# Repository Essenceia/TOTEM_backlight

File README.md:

<picture align="center">
  <source media="(prefers-color-scheme: dark)" srcset="/docs/images/TOTEM_logo_dark.svg">
  <source media="(prefers-color-scheme: light)" srcset="/docs/images/TOTEM_logo_bright.svg">
  
</picture>

<h1 align="center">T O T E M</h1>

Modified version of the wired TOTEM version 0.3 keyboard, reworked for outsourcing assembly to JLCPCB assembly services and modified to include white backlight.

## Backlight 

Adding simple white backlight to the keyboard. 
Since the default development board used as the controller doesn't have any more available pins 
the backlight could not be controlled by a key combination without the need to switch the board.

I debated removing this limitation but decided I decided to not invest the time in fixing this limitation
in favor of investing my time working on designing custom ASIC's. 

As such, the backlight intensity is controlled via a potentiometer accessible by opening the case. 

Since the switches are not symmetrical and only have an opening for the backlight led on the side opposite to the contact pins, placement 
of the led's implies switch direction. 
The original TOTEM layout gave the flexibility of placing the switch in either of two directions :
 
- pins up: connected to the switch shaft, allowing the switch to be swappable
- pins down: switches soldered in place 

I have chosen the **pins up** layout that allows the switch to still be swappable at the cost of requiring the use of the switch shaft.

:warning: The light intensity controlled circuit was dimensioned to fit these specific leds and potentiometer electrical characteristics, as such,
if you wish to re-use this design, you should **not** blindly switch the led's or the potentiometer model. 

## Manifacturability 

### Front face 

I like soldering 0603 led's as much as the next guys.

In other words: I rather do something else with my very limited time on earth, and my rumba is getting indigestion from all of the suckers that have vanished into the dust. 

Luckily, I can outsource the assembly of these components to wonderful pink and place machines, which on top of 
being more patient than me are orders of magnitude more consistent and precise. Such assembly services are 
offered directly by most big PCB manufacturers and for this board I will be going with JLCPCB. 

In order to outsource this work you will need to provide the BOM ( bill of materials ) and POS ( component position file ) files.

#### Bill of materials

Both files are human readable tables, the bill of materials file contains references to components in the JCBPCB component vendor database
as we will be purchasing the components as part of the assembly process. 

| Comment                  | Designator              | Footprint    | JLCPCB Part #（optional） |
|---------------------------|-------------------------|--------------|---------------------------|
| Diodes 1N4148W           | DL1,DL2,DL3,DL4,DL5,    | SOD-123      | C2099                     |
|                           | DL6,DL7,DL8,DL9,DL10,  |              |                           |
|                           | DL11,DL12,DL13,DL14,   |              |                           |
|                           | DL15,DL16,DL17,DL18,   |              |                           |
|                           | DL19,DR1,DR2,DR3,DR4,  |              |                           |
|                           | DR5,DR6,DR7,DR8,DR9,   |              |                           |
|                           | DR10,DR11,DR12,DR13,   |              |                           |
|                           | DR14,DR15,DR16,DR17,   |              |                           |
|                           | DR18,DR19              |              |                           |
| Reset Button, SKHLLCA010 | RSW1,RSW2               | SKHLLCA010   | C139766                   |
| TRRS jack, PJ-320A       | J1,J2                   | PJ-320A      | C2884926                  |
| LED                      | LEDL1,LEDL2,LEDL3,      | KT-0603W     | C2290                     |
|                           | LEDL4,LEDL5,LEDL6,     |              |                           |
|                           | LEDL7,LEDL8,LEDL9,     |              |                           |
|                           | LEDL10,LEDL11,LEDL12,  |              |                           |
|                           | LEDL13,LEDL14,LEDL15,  |              |                           |
|                           | LEDL16,LEDL17,LEDL18,  |              |                           |
|                           | LEDL19,LEDR1,LEDR2,    |              |                           |
|                           | LEDR3,LEDR4,LEDR5,     |              |                           |
|                           | LEDR6,LEDR7,LEDR8,     |              |                           |
|                           | LEDR9,LEDR10,LEDR11,   |              |                           |
|                           | LEDR12,LEDR13,LEDR14,  |              |                           |
|                           | LEDR15,LEDR16,LEDR17,  |              |                           |
|                           | LEDR18,LEDR19          |              |                           |
| Potenciometer            | RV1,RV2                 | GF063P1-B201 | C128076                   |

#### Positional 

The positional file instructs pick and place machines, where and in which orientation each component should be placed on the board. 
These coordinates assume the part assume the footprints on the board are similar to the footprints used in the JCBPCB part database for this part. 
For example, it assumes both footprints are aligned on the orientation of a component. 

Since there where a few disparities between the original footprints and the JCBPCB part's footprints, a few of the footprint and schematic components 
has to been updated.

There is an overview of the result with the parts we will be outsourcing assemly for outlined in blue. 

These parts are : 

- diodes
- push button
- led's
- potentiometer
- jack connectors

## Back face 

Originally, the switch footprint and the switch shaft where part of the same footprint, make it incompatible with the 
footprint coordinate offset system used to automatically generate the positional file. 
As such, I have separated the switch from the switch shaft footprint allowing the generation of a bottom positional file to also outsource
shaft assembly. 

The begin said, JLCPCB doesn't offer assembly on both sides for the time being.
Thus, given the complexity difference I will only be outsourcing assembly of the top side.   

## Paths for improvement

- Switch out the developement board in favor of having more accessible pins : 
    - re-use my known to be good stm32 circuit -> removes the need to solder on the dev board + port QMK or ZMK to board 
        - downside : design will be harder to re-use for the mechanical keyboard community as flashing the firmware now requires a JTAG
    - use another commonly used dev board as a controller 
        - downside : still requires to solder on the dev board 

- Make backlight control be more easily accessible : 
    - rework case to have the potentiometer knob accessible on the side
    - add a switch upstream of the potentiometer and rework the case to have the backlight switch accessible on the side

## Credits

Original TOTEM repo : [https://github.com/GEIGEIGEIST/TOTEM](https://github.com/GEIGEIGEIST/TOTEM)

Credit to github user `geigeigeist` for the original design

## License

This hardware is under the CERN-OHL-P v2 license, see [LICENSE.md](LICENSE.md)

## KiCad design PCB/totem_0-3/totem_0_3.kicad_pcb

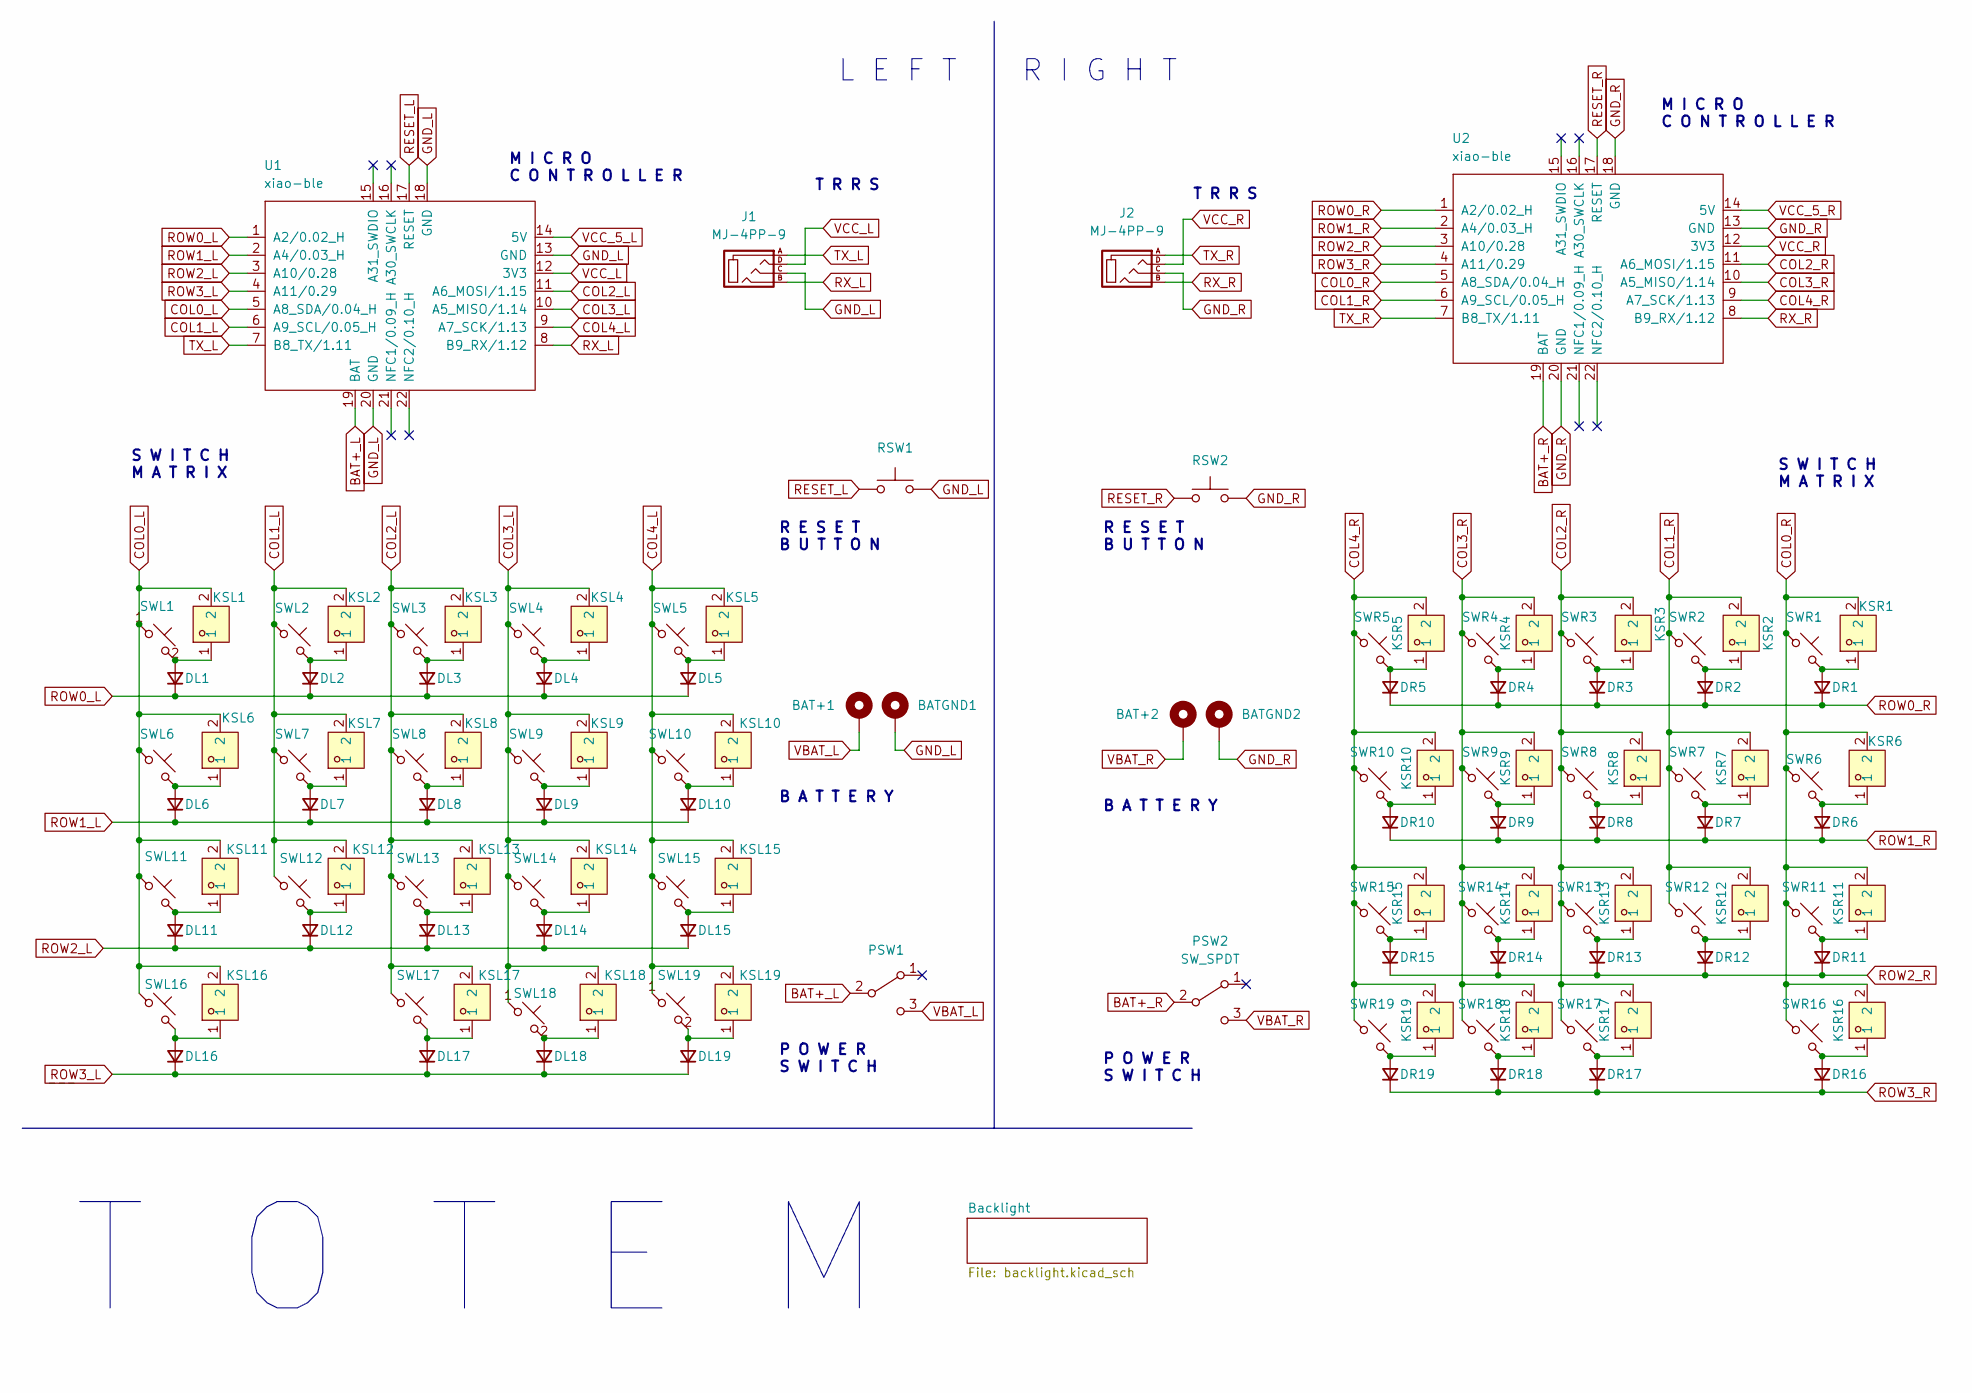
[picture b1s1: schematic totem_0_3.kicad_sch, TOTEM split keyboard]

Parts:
BAT+1, BAT+2: +; BatteryPad
BATGND1, BATGND2: -; BatteryPad
DL1, DL2, DL3, DL4, DL5, DL6, DL7, DL8, DL9, DL10, DL11, DL12, DL13, DL14, DL15, DL16, DL17, DL18, DL19: D_Small; Diode_SOD123
DR1, DR2, DR3, DR4, DR5, DR6, DR7, DR8, DR9, DR10, DR11, DR12, DR13, DR14, DR15, DR16, DR17, DR18, DR19: D_Small; Diode_SOD123
J1, J2: MJ-4PP-9; MJ-4PP-9_1side
KSL1, KSL2, KSL3, KSL4, KSL5, KSL6, KSL7, KSL8, KSL9, KSL10, KSL11, KSL12, KSL13, KSL14, KSL15, KSL16, KSL17, KSL18, KSL19: CPG135001S30; CONN-SMD_HOTPLUGPAKAGE__C9900010116; LCSC Part C5333465
KSR1, KSR2, KSR3, KSR4, KSR5, KSR6, KSR7, KSR8, KSR9, KSR10, KSR11, KSR12, KSR13, KSR14, KSR15, KSR16, KSR17, KSR18, KSR19: CPG135001S30; CONN-SMD_HOTPLUGPAKAGE__C9900010116; LCSC Part C5333465
PSW1, PSW2: SW_SPDT; MSK12C02
RSW1, RSW2: SW_Push; SKHLLCA010
SWL1, SWL2, SWL3, SWL4, SWL5, SWL6, SWL7, SWL8, SWL9, SWL10, SWL11, SWL12, SWL13, SWL14, SWL15, SWL16, SWL17, SWL18, SWL19: SW_Push_45deg; Kailh_socket_PG1350_optional
SWR1, SWR2, SWR3, SWR4, SWR5, SWR6, SWR7, SWR8, SWR9, SWR10, SWR11, SWR12, SWR13, SWR14, SWR15, SWR16, SWR17, SWR18, SWR19: SW_Push_45deg; Kailh_socket_PG1350_optional
U1, U2: xiao-ble; xiao-ble-smd-cutout

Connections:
BAT+_L: PSW1.2 (B), U1.19 (BAT)
BAT+_R: PSW2.2 (B), U2.19 (BAT)
COL0_L: KSL1.2, KSL6.2, KSL11.2, KSL16.2, SWL1.1, SWL6.1, SWL11.1, SWL16.1, U1.5 (A8_SDA/0.04_H)
COL0_R: KSR1.2, KSR6.2, KSR11.2, KSR16.2, SWR1.1, SWR6.1, SWR11.1, SWR16.1, U2.5 (A8_SDA/0.04_H)
COL1_L: KSL2.2, KSL7.2, KSL12.2, SWL2.1, SWL7.1, SWL12.1, U1.6 (A9_SCL/0.05_H)
COL1_R: KSR2.2, KSR7.2, KSR12.2, SWR2.1, SWR7.1, SWR12.1, U2.6 (A9_SCL/0.05_H)
COL2_L: KSL3.2, KSL8.2, KSL13.2, KSL17.2, SWL3.1, SWL8.1, SWL13.1, SWL17.1, U1.11 (A6_MOSI/1.15)
COL2_R: KSR3.2, KSR8.2, KSR13.2, KSR17.2, SWR3.1, SWR8.1, SWR13.1, SWR17.1, U2.11 (A6_MOSI/1.15)
COL3_L: KSL4.2, KSL9.2, KSL14.2, KSL18.2, SWL4.1, SWL9.1, SWL14.1, SWL18.1, U1.10 (A5_MISO/1.14)
COL3_R: KSR4.2, KSR9.2, KSR14.2, KSR18.2, SWR4.1, SWR9.1, SWR14.1, SWR18.1, U2.10 (A5_MISO/1.14)
COL4_L: KSL5.2, KSL10.2, KSL15.2, KSL19.2, SWL5.1, SWL10.1, SWL15.1, SWL19.1, U1.9 (A7_SCK/1.13)
COL4_R: KSR5.2, KSR10.2, KSR15.2, KSR19.2, SWR5.1, SWR10.1, SWR15.1, SWR19.1, U2.9 (A7_SCK/1.13)
GND_L: BATGND1.1, J1.C, RSW1.2, U1.13 (GND), U1.18 (GND), U1.20 (GND); also elsewhere on the board
GND_R: BATGND2.1, J2.C, RSW2.2, U2.13 (GND), U2.18 (GND), U2.20 (GND); also elsewhere on the board
unnamed: DL1.2 (A), KSL1.1, SWL1.2
unnamed: DL2.2 (A), KSL2.1, SWL2.2
unnamed: DL3.2 (A), KSL3.1, SWL3.2
unnamed: DL4.2 (A), KSL4.1, SWL4.2
unnamed: DL5.2 (A), KSL5.1, SWL5.2
unnamed: DL6.2 (A), KSL6.1, SWL6.2
unnamed: DL7.2 (A), KSL7.1, SWL7.2
unnamed: DL8.2 (A), KSL8.1, SWL8.2
unnamed: DL9.2 (A), KSL9.1, SWL9.2
unnamed: DL10.2 (A), KSL10.1, SWL10.2
unnamed: DL11.2 (A), KSL11.1, SWL11.2
unnamed: DL12.2 (A), KSL12.1, SWL12.2
unnamed: DL13.2 (A), KSL13.1, SWL13.2
unnamed: DL14.2 (A), KSL14.1, SWL14.2
unnamed: DL15.2 (A), KSL15.1, SWL15.2
unnamed: DL16.2 (A), KSL16.1, SWL16.2
unnamed: DL17.2 (A), KSL17.1, SWL17.2
unnamed: DL18.2 (A), KSL18.1, SWL18.2
unnamed: DL19.2 (A), KSL19.1, SWL19.2
unnamed: DR1.2 (A), KSR1.1, SWR1.2
unnamed: DR2.2 (A), KSR2.1, SWR2.2
unnamed: DR3.2 (A), KSR3.1, SWR3.2
unnamed: DR4.2 (A), KSR4.1, SWR4.2
unnamed: DR5.2 (A), KSR5.1, SWR5.2
unnamed: DR6.2 (A), KSR6.1, SWR6.2
unnamed: DR7.2 (A), KSR7.1, SWR7.2
unnamed: DR8.2 (A), KSR8.1, SWR8.2
unnamed: DR9.2 (A), KSR9.1, SWR9.2
unnamed: DR10.2 (A), KSR10.1, SWR10.2
unnamed: DR11.2 (A), KSR11.1, SWR11.2
unnamed: DR12.2 (A), KSR12.1, SWR12.2
unnamed: DR13.2 (A), KSR13.1, SWR13.2
unnamed: DR14.2 (A), KSR14.1, SWR14.2
unnamed: DR15.2 (A), KSR15.1, SWR15.2
unnamed: DR16.2 (A), KSR16.1, SWR16.2
unnamed: DR17.2 (A), KSR17.1, SWR17.2
unnamed: DR18.2 (A), KSR18.1, SWR18.2
unnamed: DR19.2 (A), KSR19.1, SWR19.2
RESET_L: RSW1.1, U1.17 (RESET)
RESET_R: RSW2.1, U2.17 (RESET)
ROW0_L: DL1.1 (K), DL2.1 (K), DL3.1 (K), DL4.1 (K), DL5.1 (K), U1.1 (A2/0.02_H)
ROW0_R: DR1.1 (K), DR2.1 (K), DR3.1 (K), DR4.1 (K), DR5.1 (K), U2.1 (A2/0.02_H)
ROW1_L: DL6.1 (K), DL7.1 (K), DL8.1 (K), DL9.1 (K), DL10.1 (K), U1.2 (A4/0.03_H)
ROW1_R: DR6.1 (K), DR7.1 (K), DR8.1 (K), DR9.1 (K), DR10.1 (K), U2.2 (A4/0.03_H)
ROW2_L: DL11.1 (K), DL12.1 (K), DL13.1 (K), DL14.1 (K), DL15.1 (K), U1.3 (A10/0.28)
ROW2_R: DR11.1 (K), DR12.1 (K), DR13.1 (K), DR14.1 (K), DR15.1 (K), U2.3 (A10/0.28)
ROW3_L: DL16.1 (K), DL17.1 (K), DL18.1 (K), DL19.1 (K), U1.4 (A11/0.29)
ROW3_R: DR16.1 (K), DR17.1 (K), DR18.1 (K), DR19.1 (K), U2.4 (A11/0.29)
RX_L: J1.B, U1.8 (B9_RX/1.12)
RX_R: J2.B, U2.8 (B9_RX/1.12)
TX_L: J1.A, U1.7 (B8_TX/1.11)
TX_R: J2.A, U2.7 (B8_TX/1.11)
VBAT_L: BAT+1.1, PSW1.3 (C)
VBAT_R: BAT+2.1, PSW2.3 (C)
VCC_5_L: U1.14 (5V); also elsewhere on the board
VCC_5_R: U2.14 (5V); also elsewhere on the board
VCC_L: J1.D, U1.12 (3V3)
VCC_R: J2.D, U2.12 (3V3)

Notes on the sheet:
M I C R O C O N T R O L L E R
T R R S
R E S E T B U T T O N
S W I T C H M A T R I X
P O W E R S W I T C H
T O T E M
B A T T E R Y
R I G H T
L E F T

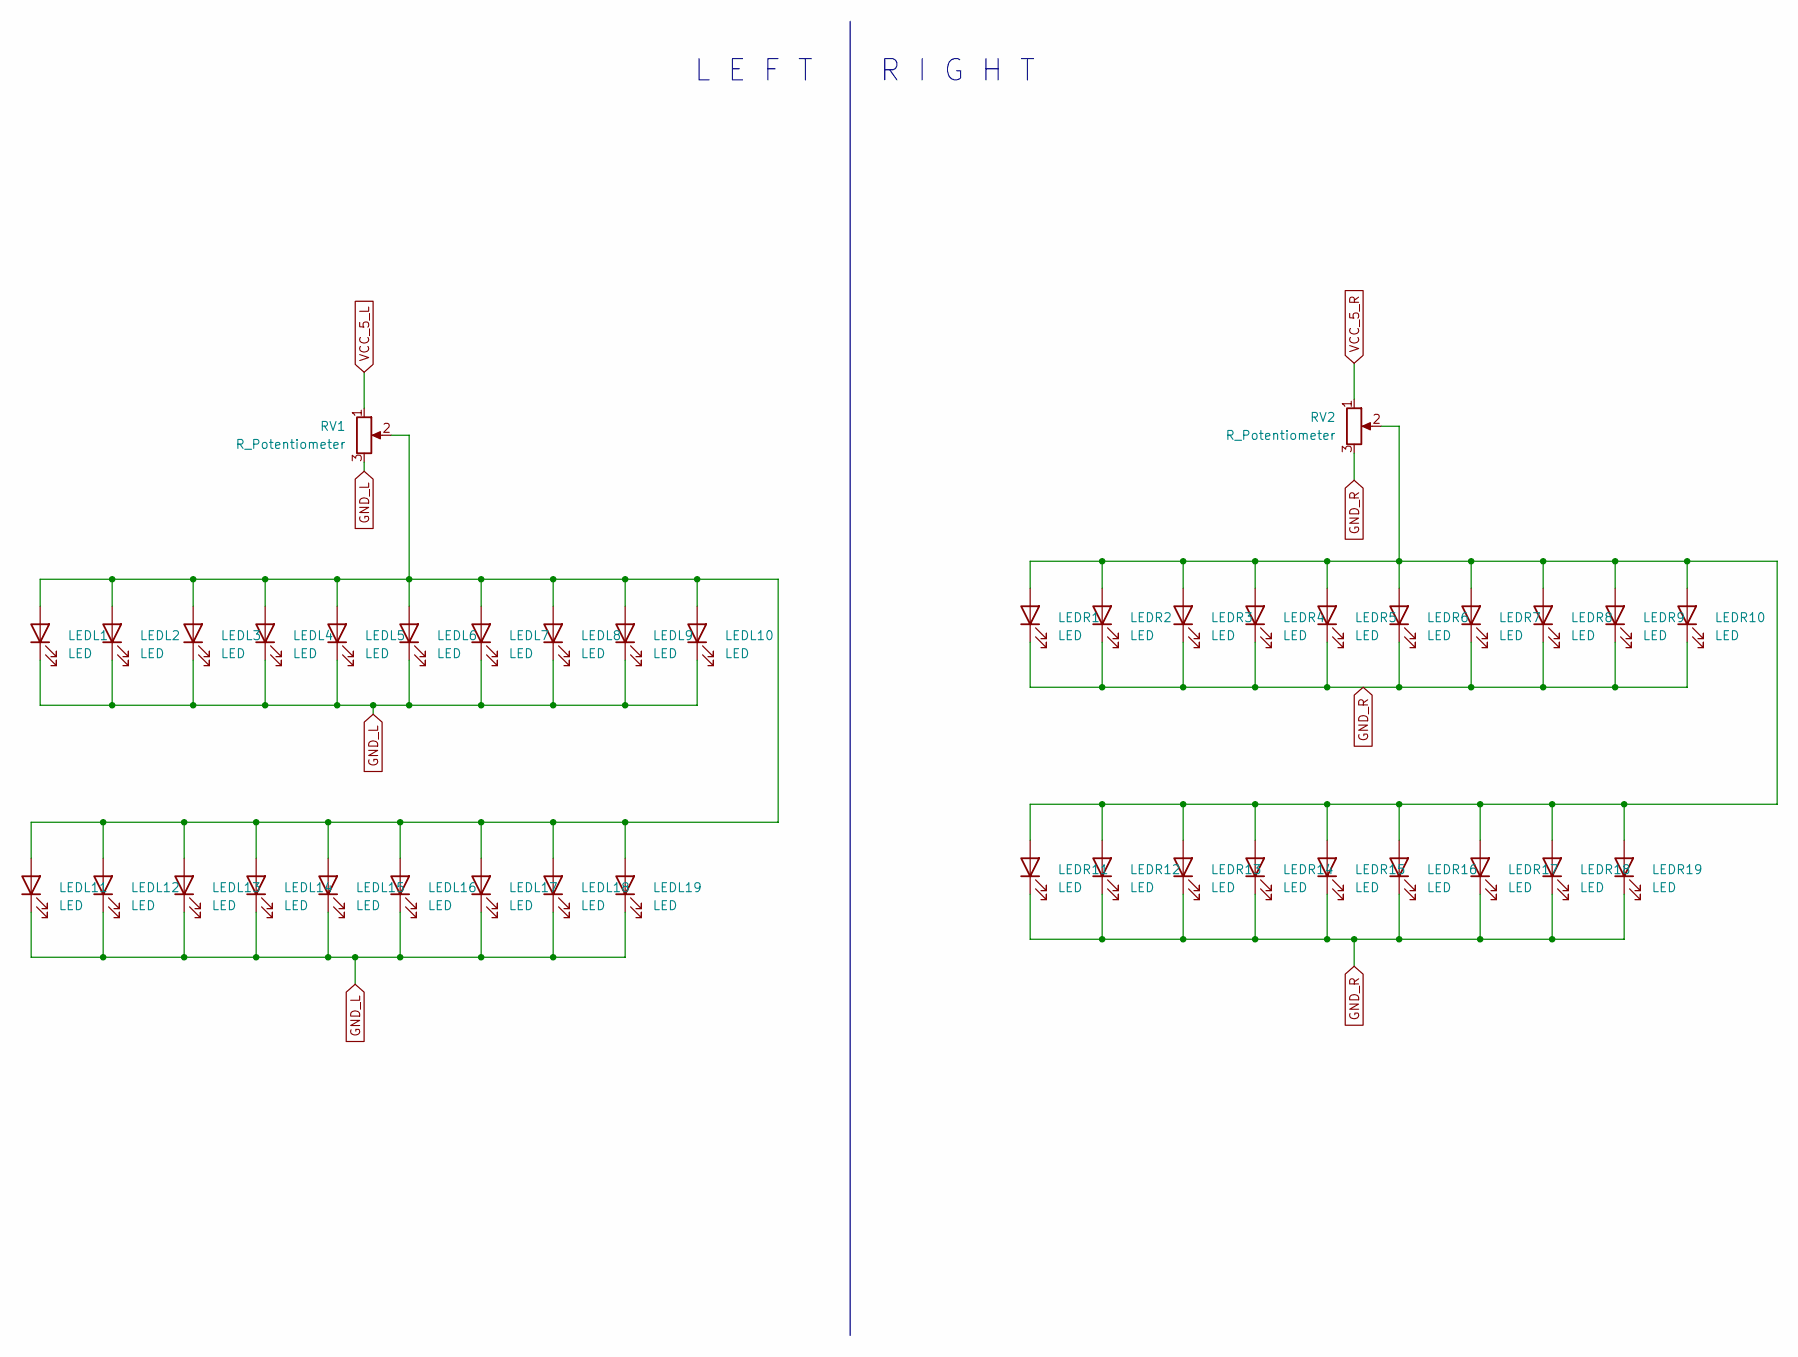
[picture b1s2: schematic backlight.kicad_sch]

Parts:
LEDL1, LEDL2, LEDL3, LEDL4, LEDL5, LEDL6, LEDL7, LEDL8, LEDL9, LEDL10, LEDL11, LEDL12, LEDL13, LEDL14, LEDL15, LEDL16, LEDL17, LEDL18, LEDL19: LED; LED0603-R-RD_WHITE
LEDR1, LEDR2, LEDR3, LEDR4, LEDR5, LEDR6, LEDR7, LEDR8, LEDR9, LEDR10, LEDR11, LEDR12, LEDR13, LEDR14, LEDR15, LEDR16, LEDR17, LEDR18, LEDR19: LED; LED0603-R-RD_WHITE
RV1, RV2: R_Potentiometer; RES-ADJ-SMD_GF063P1

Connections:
GND_L: LEDL1.1 (K), LEDL2.1 (K), LEDL3.1 (K), LEDL4.1 (K), LEDL5.1 (K), LEDL6.1 (K), LEDL7.1 (K), LEDL8.1 (K), LEDL9.1 (K), LEDL10.1 (K), LEDL11.1 (K), LEDL12.1 (K), LEDL13.1 (K), LEDL14.1 (K), LEDL15.1 (K), LEDL16.1 (K), LEDL17.1 (K), LEDL18.1 (K), LEDL19.1 (K), RV1.3; also elsewhere on the board
GND_R: LEDR1.1 (K), LEDR2.1 (K), LEDR3.1 (K), LEDR4.1 (K), LEDR5.1 (K), LEDR6.1 (K), LEDR7.1 (K), LEDR8.1 (K), LEDR9.1 (K), LEDR10.1 (K), LEDR11.1 (K), LEDR12.1 (K), LEDR13.1 (K), LEDR14.1 (K), LEDR15.1 (K), LEDR16.1 (K), LEDR17.1 (K), LEDR18.1 (K), LEDR19.1 (K), RV2.3; also elsewhere on the board
unnamed: LEDL1.2 (A), LEDL2.2 (A), LEDL3.2 (A), LEDL4.2 (A), LEDL5.2 (A), LEDL6.2 (A), LEDL7.2 (A), LEDL8.2 (A), LEDL9.2 (A), LEDL10.2 (A), LEDL11.2 (A), LEDL12.2 (A), LEDL13.2 (A), LEDL14.2 (A), LEDL15.2 (A), LEDL16.2 (A), LEDL17.2 (A), LEDL18.2 (A), LEDL19.2 (A), RV1.2
unnamed: LEDR1.2 (A), LEDR2.2 (A), LEDR3.2 (A), LEDR4.2 (A), LEDR5.2 (A), LEDR6.2 (A), LEDR7.2 (A), LEDR8.2 (A), LEDR9.2 (A), LEDR10.2 (A), LEDR11.2 (A), LEDR12.2 (A), LEDR13.2 (A), LEDR14.2 (A), LEDR15.2 (A), LEDR16.2 (A), LEDR17.2 (A), LEDR18.2 (A), LEDR19.2 (A), RV2.2
VCC_5_L: RV1.1; also elsewhere on the board
VCC_5_R: RV2.1; also elsewhere on the board

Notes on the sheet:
R I G H T
L E F T

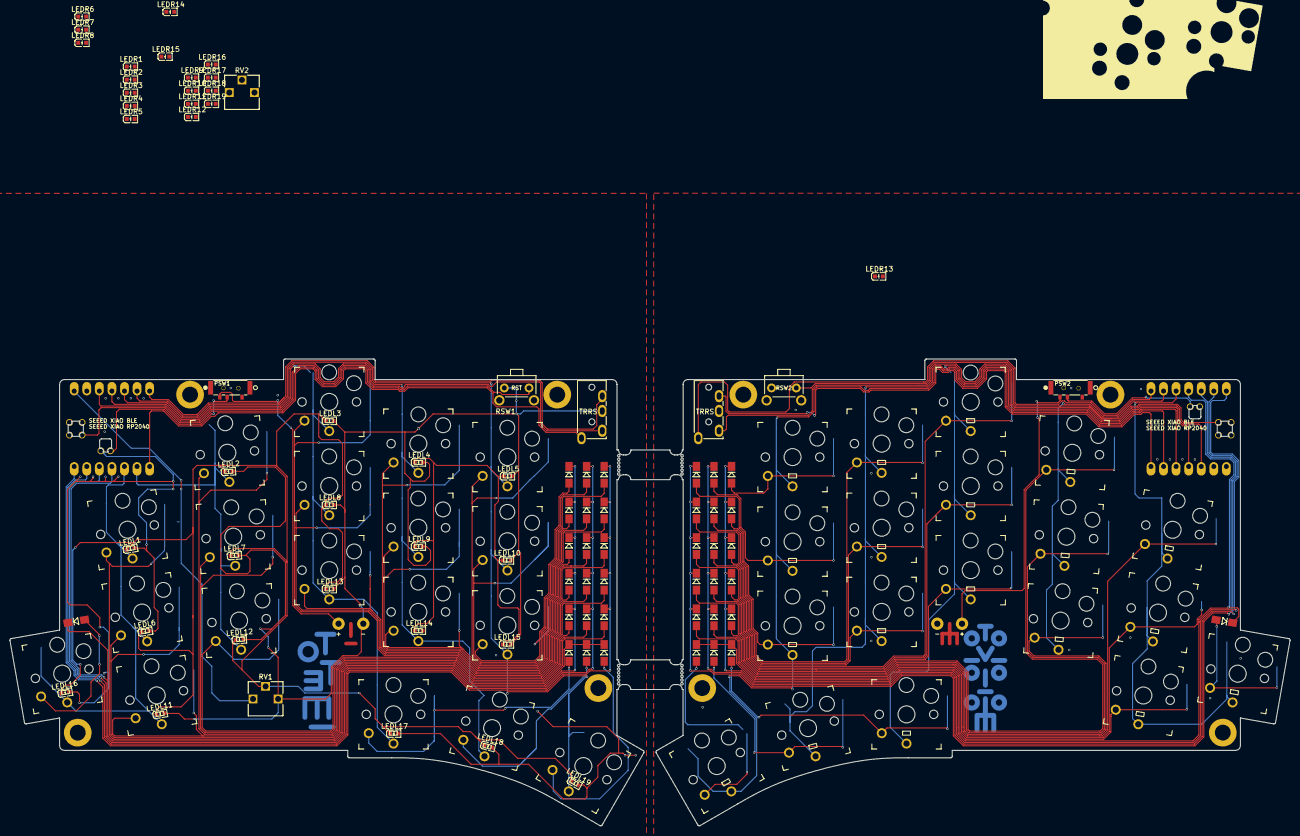
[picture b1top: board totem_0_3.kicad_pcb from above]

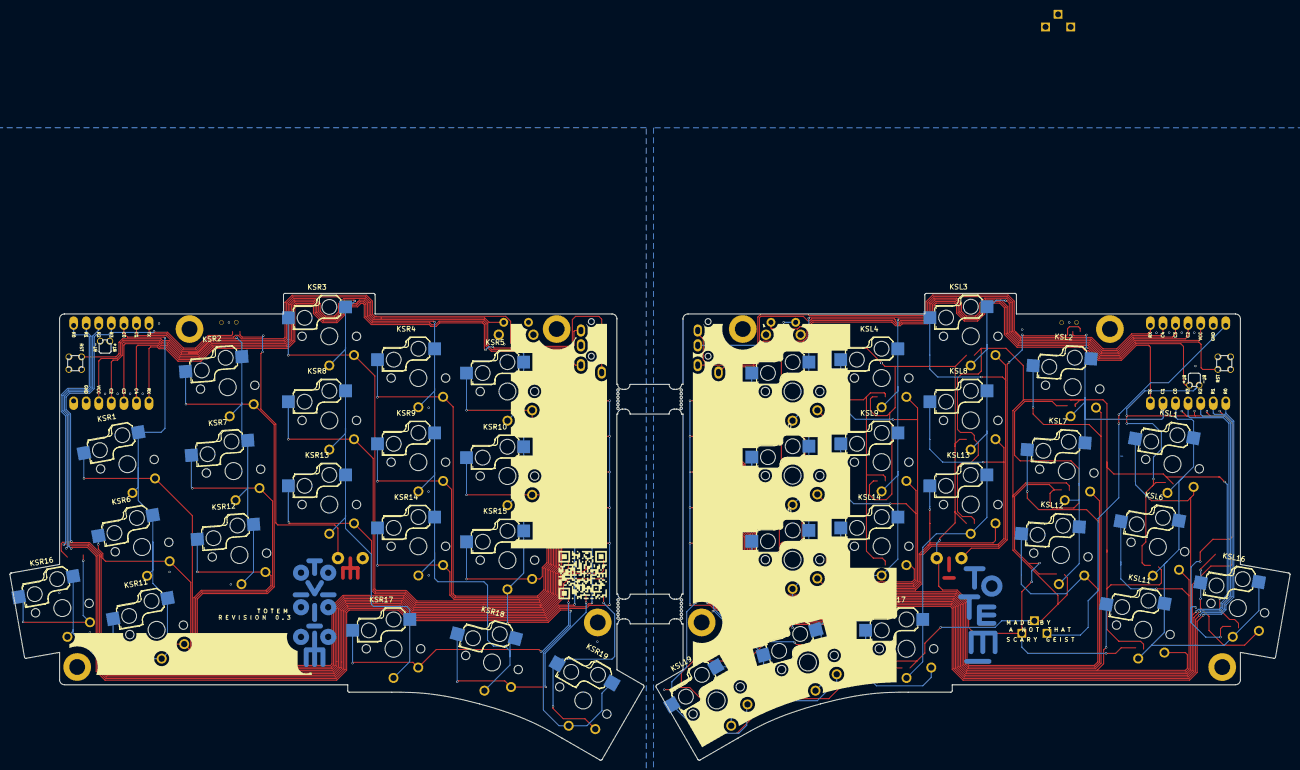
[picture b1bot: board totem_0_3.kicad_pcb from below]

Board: 2 copper layers, 258.7 x 94.4 mm, 166 parts (38 on the bottom side), 74 nets.

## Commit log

2025-08-25 optimising for manifacturability at jlc pcb, seperating connectors from switch footprint
2025-08-26 finished adding switch sockets in the original positions
2025-08-26 adding leds to left, wip
2025-08-27 Adding backlight shematics, wiring left hand, wip
2025-08-28 Finishing wiring, generating placement files for pick and place, modified footprints due to wrong footprint corrdingates at jlcpcb
2025-08-28 add new footprints
2025-08-28 updated backlight shematics with new leds, default led uses reversed pin number assigns, aka : leds get mounted backwards by pick and place, what a tragedy
2025-08-28 updating kicad footprint and shematics
2025-08-28 Updating readme to talk about changes, wip
2025-08-28 Update readme, update gerber renders
2025-08-29 update readme, wip
2025-08-29 Update readme, update license, keep original attribution (naturally)
2025-08-29 layout
2025-08-29 add routing illustration
2025-08-29 illustration of the 0603 layout, yes, in mm
2025-08-29 make table less wide
2025-08-29 clean readme
2025-08-29 clean license file
2025-08-29 newline
